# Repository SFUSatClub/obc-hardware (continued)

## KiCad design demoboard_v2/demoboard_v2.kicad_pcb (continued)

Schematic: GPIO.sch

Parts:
D3: LED; L_0402
Q5: DMN2075U; SOT23_DMN2075U
R8, R26: 10k; R_0402
R9: 100; R_0402
U1: TMS570LS0714; LQFP-144_20x20mm_Pitch0.5mm
W13: WD_TEST; Test_Point

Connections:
1v2: U1.17, U1.29, U1.45, U1.48, U1.49, U1.57, U1.87, U1.101, U1.114, U1.123, U1.137, U1.143; also elsewhere on the board
3v3: R9.1, U1.10, U1.26, U1.42, U1.66, U1.69, U1.104, U1.120, U1.134, U1.136; also elsewhere on the board
AD1_3: U1.74; also elsewhere on the board
AD1_4: U1.76; also elsewhere on the board
AD1_5: U1.78; also elsewhere on the board
AD1_6: U1.80; also elsewhere on the board
AD1_7: U1.61; also elsewhere on the board
AD1_8: U1.83; also elsewhere on the board
AD1_9: U1.70; also elsewhere on the board
AD1_10: U1.72; also elsewhere on the board
FLASH0_CS: U1.105; also elsewhere on the board
FLASH1_CS: U1.130; also elsewhere on the board
FLASH2_CS: U1.40; also elsewhere on the board
FLASH_CLK: U1.95; also elsewhere on the board
FLASH_MISO: U1.94; also elsewhere on the board
FLASH_MOSI: U1.93; also elsewhere on the board
GIOA0: U1.2; also elsewhere on the board
GIOA1: U1.5
GIOA2: U1.9
GIOA6: Q5.2 (G), R8.1, U1.16
GIOA7: U1.22
GIOB1: U1.133; also elsewhere on the board
GIOB2: U1.142; also elsewhere on the board
GIOB3: U1.1; also elsewhere on the board
GND: Q5.3 (S), R8.2, R26.2, U1.11, U1.21, U1.27, U1.28, U1.34, U1.43, U1.44, U1.47, U1.50, U1.56, U1.67, U1.68, U1.88, U1.102, U1.103, U1.115, U1.121, U1.122, U1.135, U1.138, U1.144; also elsewhere on the board
I2C_SCL: U1.3; also elsewhere on the board
I2C_SDA: U1.4; also elsewhere on the board
INA_OUT: U1.73; also elsewhere on the board
MASTER_RESET: U1.46; also elsewhere on the board
NHET1_4: U1.36; also elsewhere on the board
NHET1_7: U1.33; also elsewhere on the board
NHET1_22: U1.15; also elsewhere on the board
NHET1_26: U1.92; also elsewhere on the board
unnamed 40: U1.19; also elsewhere on the board
unnamed 41: U1.18; also elsewhere on the board
unnamed 42: U1.20; also elsewhere on the board
unnamed 44: U1.116; also elsewhere on the board
unnamed: D3.1, Q5.1 (D)
unnamed: D3.2, R9.2
unnamed 86: U1.97; also elsewhere on the board
unnamed 93: U1.55; also elsewhere on the board
unnamed 107: U1.86; also elsewhere on the board
unnamed 112: U1.117; also elsewhere on the board
RF_ADC1: U1.60; also elsewhere on the board
RF_ADC2: U1.71; also elsewhere on the board
RF_CLK: U1.53; also elsewhere on the board
RF_CS: U1.37; also elsewhere on the board
RF_GAIN_CS: U1.6; also elsewhere on the board
RF_MISO: U1.51; also elsewhere on the board
RF_MOSI: U1.52; also elsewhere on the board
RF_PWM1: U1.140; also elsewhere on the board
RF_PWM2: U1.141; also elsewhere on the board
RTCK: U1.113; also elsewhere on the board
RTC_CLK: U1.25; also elsewhere on the board
RTC_CS: U1.24; also elsewhere on the board
RTC_MISO: U1.31; also elsewhere on the board
RTC_MOSI: U1.30; also elsewhere on the board
SPI5_CLK: U1.100; also elsewhere on the board
SPI5_CS0: U1.32; also elsewhere on the board
SPI5_MISO: U1.98; also elsewhere on the board
SPI5_MOSI: U1.99; also elsewhere on the board
TCK: U1.112; also elsewhere on the board
TDI: U1.110; also elsewhere on the board
TDO: U1.111; also elsewhere on the board
TMS: U1.108; also elsewhere on the board
UART_RX: U1.38; also elsewhere on the board
UART_TX: U1.39; also elsewhere on the board
WATCHDOG: R26.1, U1.126, W13.1; also elsewhere on the board
nTRST: U1.109; also elsewhere on the board

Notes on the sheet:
"Pin 16 LED" - for blinky debug

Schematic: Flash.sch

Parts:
C24, C25, C26: 0.1µF; C_0402
P9: FLASH_SPI; 3x_01In_Header_v2
P10: FLASH_CS; 3x_01In_Header_v2
R10, R11, R13, R14, R15, R17, R18, R19, R21: 10k; R_0402
R12, R16, R20: 0; R_0402
U5, U6, U7: FLASH_IS25LP016D; SOT-8_208mil_medium
W1, W2, W3, W4, W5, W6: TEST_1P; Test_Point

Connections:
3v3: C24.2, C25.2, C26.2, R11.1, R13.1, R15.1, R17.1, R19.1, R21.1, U5.8, U6.8, U7.8; also elsewhere on the board
FLASH0_CS: P10.3, R11.2, U5.1; also elsewhere on the board
FLASH1_CS: P10.2, R15.2, U6.1; also elsewhere on the board
FLASH2_CS: P10.1, R19.2, U7.1; also elsewhere on the board
FLASH_CLK: P9.1, U5.6, U6.6, U7.6; also elsewhere on the board
FLASH_MISO: P9.2, U5.2, U6.2, U7.2; also elsewhere on the board
FLASH_MOSI: P9.3, U5.5, U6.5, U7.5; also elsewhere on the board
GND: C24.1, C25.1, C26.1, R10.2, R14.2, R18.2, U5.4, U6.4, U7.4; also elsewhere on the board
MASTER_RESET: R12.1, R16.1, R20.1; also elsewhere on the board
unnamed: R10.1, U5.3, W1.1
unnamed: R12.2, R13.2, U5.7, W2.1
unnamed: R14.1, U6.3, W3.1
unnamed: R16.2, R17.2, U6.7, W4.1
unnamed: R18.1, U7.3, W5.1
unnamed: R20.2, R21.2, U7.7, W6.1

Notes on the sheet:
Note: Only connect one of these at once. MASTER_RESET enables simultaneous memory and processor reset, with appropriate bits set.
Triple redundant memory with configurable hold/reset. Hold will pause comms, reset will reset and can be set to be synchronous with processor reset through MASTER_RESET

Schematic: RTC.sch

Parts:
C29: 10nF; C_0402
C30: 470µF; Supercap_v2
P8: RTC_SPI; 4x01In_Header_v2
U8: AB-RTCMC-EOA9-S3; RTC_AB-RTCMC_EA09_S3
W9: CLKOUT; Test_Point
W10: RTC_OE; Test_Point
W11: RTC_INT; Test_Point

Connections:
3v3: C29.1, U8.2 (VDD); also elsewhere on the board
GND: C29.2, C30.2, U8.6 (GND); also elsewhere on the board
unnamed: C30.1, U8.9 (Vbackup)
unnamed: U8.1 (CLKOE), W10.1
unnamed: U8.3 (CLKOUT), W9.1
unnamed: U8.7 (INT), W11.1
RTC_CLK: P8.2, U8.4 (SCL); also elsewhere on the board
RTC_CS: P8.1, U8.8 (CE); also elsewhere on the board
RTC_MISO: P8.3, U8.5 (SDO); also elsewhere on the board
RTC_MOSI: P8.4, U8.10 (SDI); also elsewhere on the board

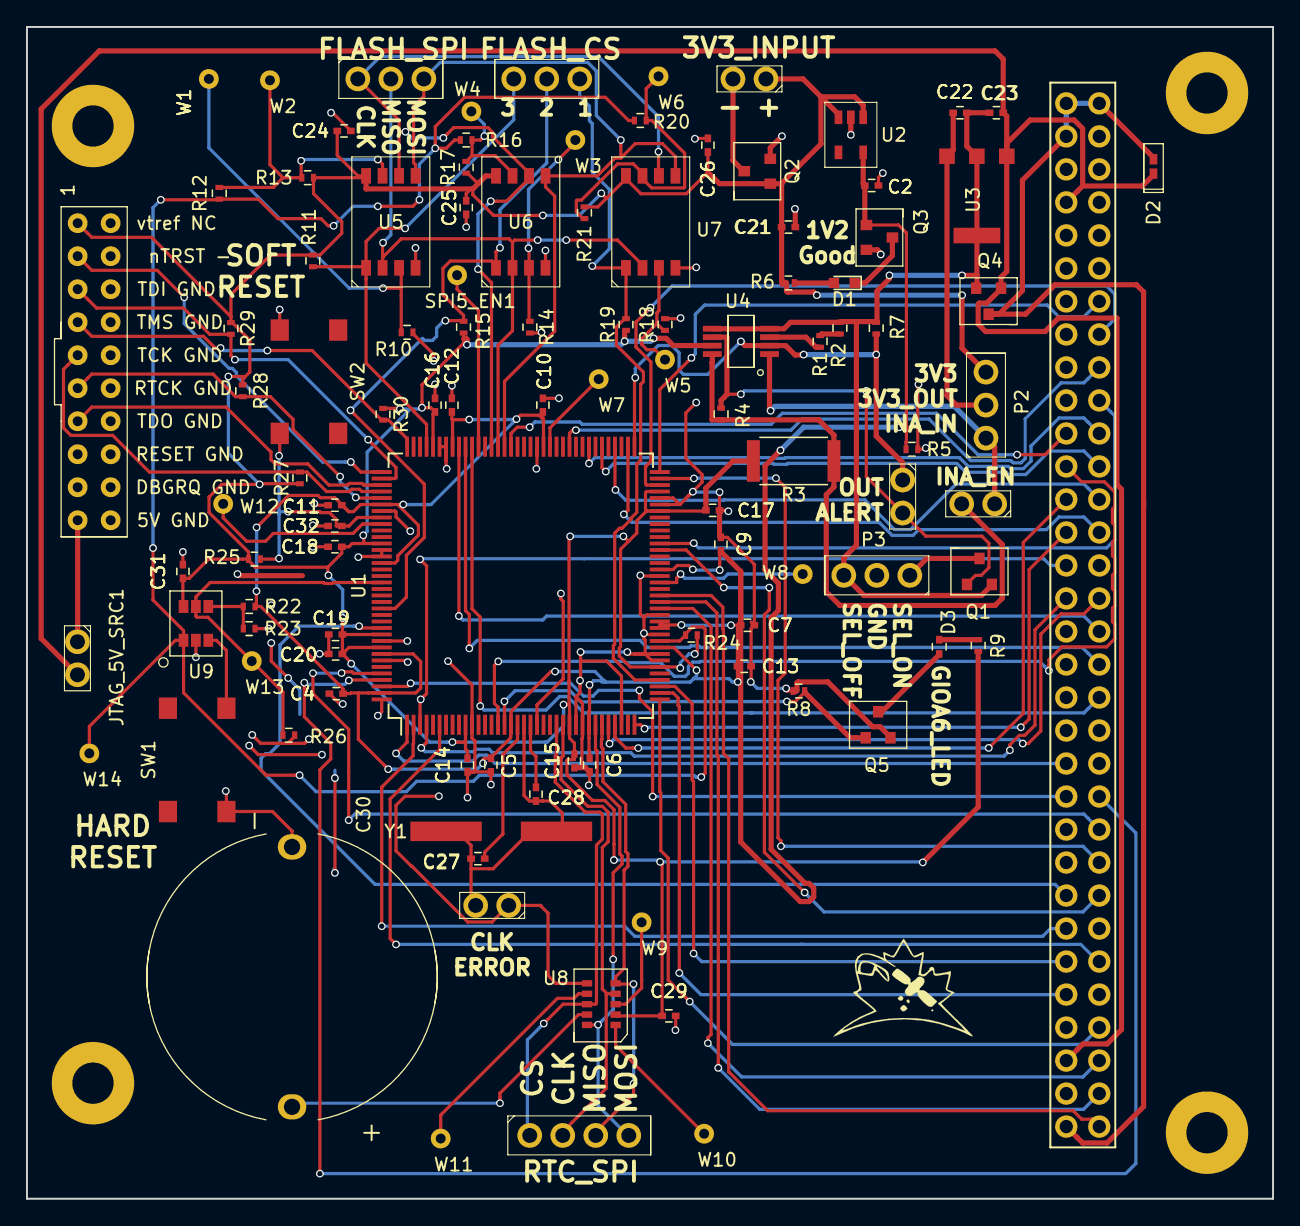
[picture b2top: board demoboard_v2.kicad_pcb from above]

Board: 2 copper layers, 95.9 x 90.2 mm, 107 parts (0 on the bottom side), 92 nets.

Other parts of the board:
SPI5_EN1: TEST_1P; Test_Point
W1#2: TEST_1P; Test_Point

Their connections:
unnamed 86: SPI5_EN1.1; also elsewhere on the board

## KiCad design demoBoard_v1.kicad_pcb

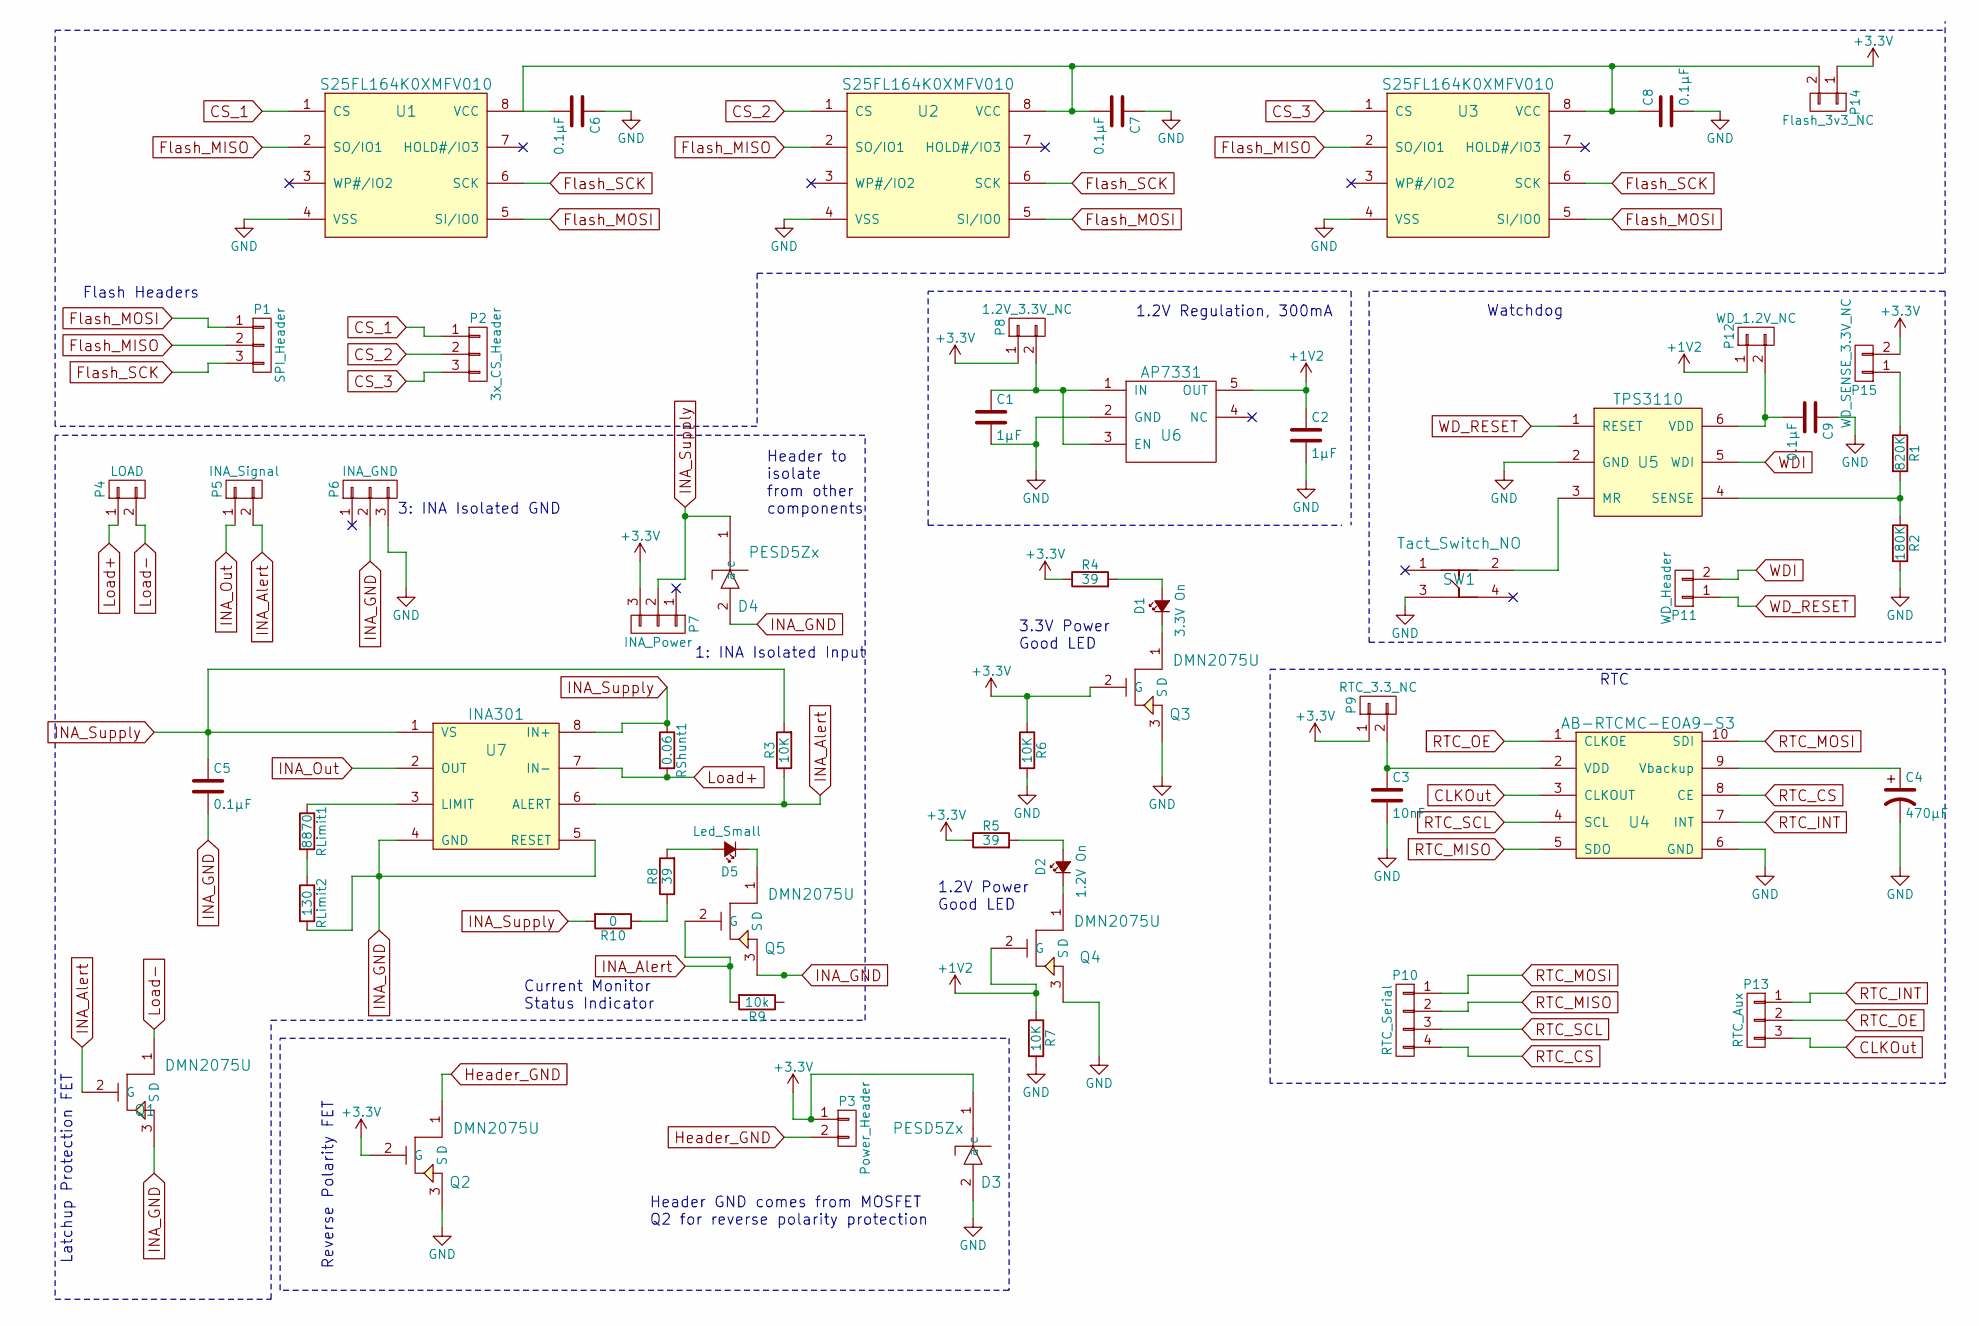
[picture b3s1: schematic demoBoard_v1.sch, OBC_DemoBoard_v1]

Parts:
C1, C2: 1µF; C_0402
C3: 10nF; C_0402
C4: 470µF; Supercap_v2
C5, C6, C7, C8, C9: 0.1µF; C_0402
D1: 3.3V On; LED_150060GS75000
D2: 1.2V On; LED_150060GS75000
D3, D4: PESD5Zx; PESD57zx
D5: Led_Small; LED_150060GS75000
P1: SPI_Header; 3x_01In_Header_v2
P2: 3x_CS_Header; 3x_01In_Header_v2
P3: Power_Header; 2x01In_Header_v2
P4: LOAD; 2x01In_Header_v2
P5: INA_Signal; 2x01In_Header_v2
P6: INA_GND; 3x_01In_Header_v2
P7: INA_Power; 3x_01In_Header_v2
P8: 1.2V_3.3V_NC; 2x01In_Header_v2
P9: RTC_3.3_NC; 2x01In_Header_v2
P10: RTC_Serial; 4x01In_Header_v2
P11: WD_Header; 2x01In_Header_v2
P12: WD_1.2V_NC; 2x01In_Header_v2
P13: RTC_Aux; 3x_01In_Header_v2
P14: Flash_3v3_NC; 2x01In_Header_v2
P15: WD_SENSE_3.3V_NC; 2x01In_Header_v2
Q1, Q2, Q3, Q4, Q5: DMN2075U; SOT23_DMN2075U
R1: 820K; R_0402
R2: 180K; R_0402
R3, R6, R7: 10K; R_0402
R4, R5, R8: 39; R_0402
R9: 10k; R_0402
R10: 0; R_0402
RLimit1: 8870; R_0402
RLimit2: 130; R_0402
RShunt1: 0.06; R_2512
SW1: Tact_Switch_NO; Tact_SW_SMD
U1, U2, U3: S25FL164K0XMFV010; SOT-8_208mil_medium
U4: AB-RTCMC-EOA9-S3; RTC_AB-RTCMC_EA09_S3
U5: TPS3110; SOT_23_6
U6: AP7331; SOT25
U7: INA301; VSSOP_8

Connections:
+1V2: C2.1, P12.1, Q4.2 (G), R7.1, U6.5 (OUT)
+3V3: D3.1 (c), P3.1, P7.3, P8.1, P9.1, P14.1, P15.2, Q2.2 (G), Q3.2 (G), R4.1, R5.1, R6.1
CLKOut: P13.3, U4.3 (CLKOUT)
CS_1: P2.1, U1.1 (CS)
CS_2: P2.2, U2.1 (CS)
CS_3: P2.3, U3.1 (CS)
Flash_MISO: P1.2, U1.2 (SO/IO1), U2.2 (SO/IO1), U3.2 (SO/IO1)
Flash_MOSI: P1.1, U1.5 (SI/IO0), U2.5 (SI/IO0), U3.5 (SI/IO0)
Flash_SCK: P1.3, U1.6 (SCK), U2.6 (SCK), U3.6 (SCK)
GND: C1.2, C2.2, C3.2, C4.2, C6.1, C7.1, C8.2, C9.1, D3.2 (a), P6.3, Q2.3 (S), Q3.3 (S), Q4.3 (S), R2.2, R6.2, R7.2, SW1.3, U1.4 (VSS), U2.4 (VSS), U3.4 (VSS), U4.6 (GND), U5.2 (GND), U6.2 (GND)
Header_GND: P3.2, Q2.1 (D)
INA_Alert: P5.2, Q1.2 (G), Q5.2 (G), R3.1, R9.2, U7.6 (ALERT)
INA_GND: C5.2, D4.2 (a), P6.2, Q1.3 (S), Q5.3 (S), R9.1, RLimit2.2, U7.4 (GND), U7.5 (RESET)
INA_Out: P5.1, U7.2 (OUT)
INA_Supply: C5.1, D4.1 (c), P7.2, R3.2, R10.2, RShunt1.1, U7.1 (VS), U7.8 (IN+)
Load+: P4.1, RShunt1.2, U7.7 (IN-)
Load-: P4.2, Q1.1 (D)
unnamed: C1.1, P8.2, U6.1 (IN), U6.3 (EN)
unnamed: C3.1, P9.2, U4.2 (VDD)
unnamed: C4.1, U4.9 (Vbackup)
unnamed: C6.2, C7.2, C8.1, P14.2, U1.8 (VCC), U2.8 (VCC), U3.8 (VCC)
unnamed: C9.2, P12.2, U5.6 (VDD)
unnamed: D1.1 (K), Q3.1 (D)
unnamed: D1.2 (A), R4.2
unnamed: D2.1 (K), Q4.1 (D)
unnamed: D2.2 (A), R5.2
unnamed: D5.1 (K), Q5.1 (D)
unnamed: D5.2 (A), R8.2
unnamed: P15.1, R1.1
unnamed: R1.2, R2.1, U5.4 (SENSE)
unnamed: R8.1, R10.1
unnamed: RLimit1.1, U7.3 (LIMIT)
unnamed: RLimit1.2, RLimit2.1
unnamed: SW1.2, U5.3 (MR)
RTC_CS: P10.4, U4.8 (CE)
RTC_INT: P13.1, U4.7 (INT)
RTC_MISO: P10.2, U4.5 (SDO)
RTC_MOSI: P10.1, U4.10 (SDI)
RTC_OE: P13.2, U4.1 (CLKOE)
RTC_SCL: P10.3, U4.4 (SCL)
WDI: P11.2, U5.5 (WDI)
WD_RESET: P11.1, U5.1 (RESET)

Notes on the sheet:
Watchdog
Flash Headers
1.2V Regulation, 300mA
RTC
Header to isolate from other components
1: INA Isolated Input
3: INA Isolated GND
Header GND comes from MOSFET Q2 for reverse polarity protection
Latchup Protection FET
Reverse Polarity FET
3.3V Power Good LED
1.2V Power Good LED
Current Monitor Status Indicator

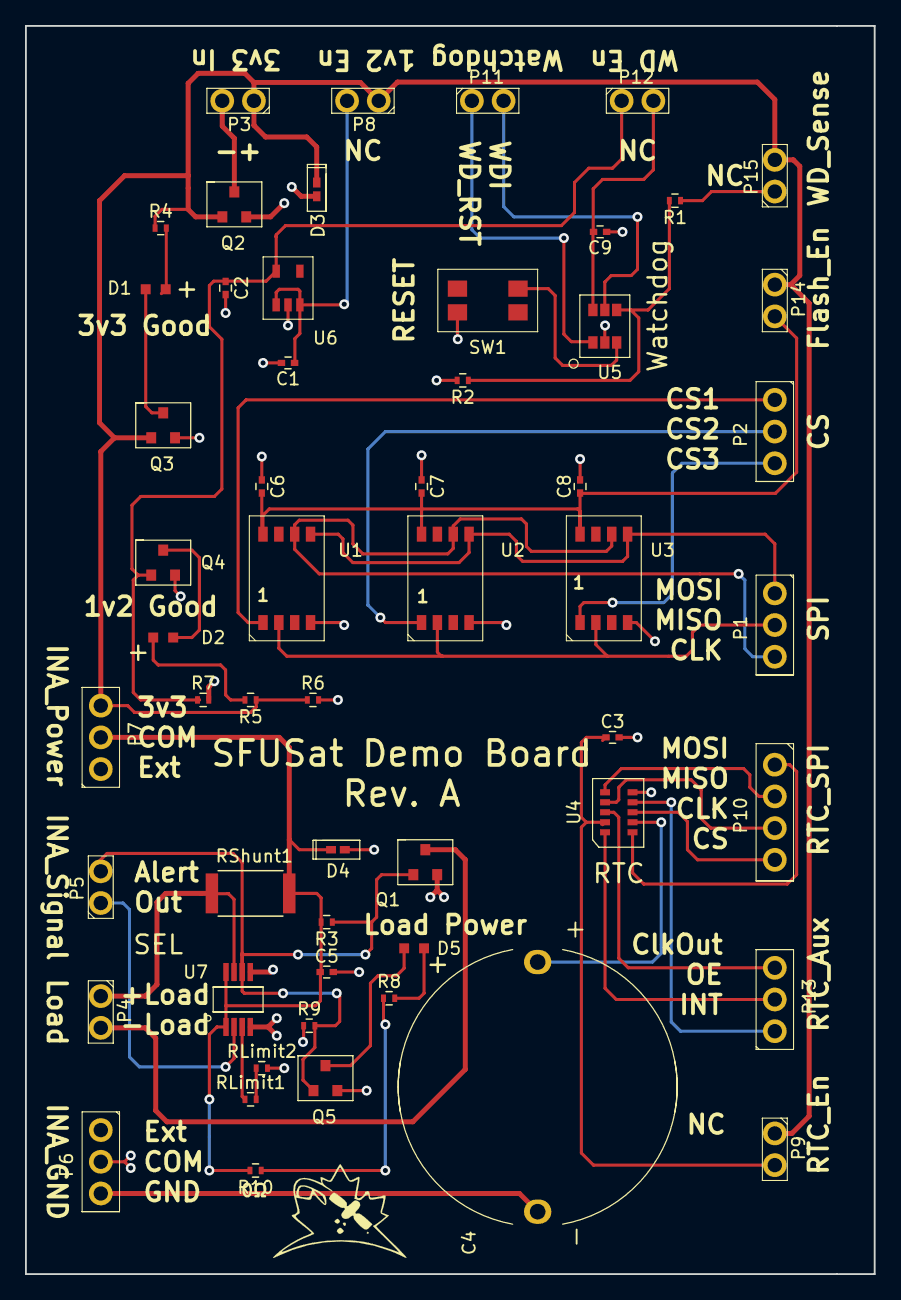
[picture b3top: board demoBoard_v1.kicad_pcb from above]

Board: 2 copper layers, 68.0 x 100.0 mm, 55 parts (0 on the bottom side), 42 nets.

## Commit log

2017-05-10 removed submodule
2017-05-11 added memory interfce and started watchdog
2017-05-19 Nearly done, todo: fix current shunt, add LEDs, add footprints and make PCB
2017-05-22 Todo: change MOSFET and add indicator LEDs
2017-05-22 Updated FET, added indicator LEDs on 3.3v and 1.2v rails.
2017-05-22 Beginning board layout
2017-05-22 Finished initial PCB layout
2017-05-23 Starting to redo things after this commit.
2017-05-23 Cleaned up and made the board smaller. Began adding silkscreen
2017-05-24 Added separate ground pane for SEL monitor to facilitate independent testing of it. Beefed up power tracks. Discovered error with external load connection being shorted to ground at the connector, an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
2017-05-24 Fixed SEL monitor mistake ground connection
2017-05-24 Added more silkscreens including the logo. Reorganized some traces
2017-05-24 Added TVS and INA indicator LED to schematic. Committing before adding footprint and PCB traces.
2017-05-24 Ready to be sent to board house
2017-05-24 Ready to be sent to board house. Last minute changed via size to be safe.
2017-05-24 moved some vias to avoid a silkscreen
2017-05-25 Added gerbers
2017-05-25 add gitignore and update kicad-lib
2017-05-25 fixed gitignore
2017-05-25 Fixed gitignore again lol
2017-05-25 Updated LED resistors to 30 ohm, turned RLimit1 into RLimit1 and RLimit2 which are values you can actually buy. Made pin header holes slightly bigger, regenerated gerbers
2017-05-25 Updated footprints for headers in schematic
2017-05-25 Updated pad clearance to 0.075mm, regenerated gerbers
2017-05-28 Updated footprint lib with solder paste apertures
2017-06-04 Updated submodule KiCad-Lib
2017-06-04 Updated DMN2075 MOSFET symbol
2017-06-04 Updated 0402 capacitor in library. Haven't updated footprints on PCB, although they could be changed.
2017-06-04 Decided to update 0402 resistors and caps to good SFUSat footprints.
2017-06-09 Added LSO743x schematic (not done yet)
2017-06-23 updated Kicad lib with RF changes
2017-06-23 Started new project for board v2, updated footprint for RTC, added all pins of TMS570LS0432
2017-06-30 Added 104 connector, put 104 footprint in PCB and have decoupling caps for the mcu.
2017-06-30 Added RF SPI to schematic
2017-06-30 Added schematics for MCU support
2017-07-04 Beginning to add latchup circuit. Latchup protection can be disabled with jumpers, and now has a current limit of 800mA
2017-07-04 Completed power jumper setup for SEL monitor
2017-07-07 3v3 reverse polarity FET, connected current monitor to ADC, defined RF PWM and ADC pins on 104 connector, added UART connector, pc104 reverse polarity FET, 104 connector TVS diode.
2017-07-12 Added debug LED and 1v2 good LED
2017-07-13 Finished flash memory schematic, added pin 16 LED and 1v2 good LED
2017-07-14 Added clock, RTC, flash serial connections
2017-07-20 Finished watchdog circuit. Todo: add footprint for tact switch, i2c, UART, USB connector
2017-07-21 Beginning board layout.
2017-07-21 Connect RTC CS, CLK, MISO, MOSI
2017-07-21 Checked design rules, placed decoupling for MCU. Beginning placement
2017-07-23 JTAG header added.
2017-07-23 Almost done the layout
2017-07-23 Board layout nearly done - need to add USB jack
2017-07-23 Finished initial layout. USB port added.
2017-07-25 Updating to recent changes
2017-07-25 I think I fixed the mess with the Kicad-Lib submodule
2017-07-25 Removed old nasty Kicad lib from demoboard_v2 directory
2017-07-25 Cleaned up directory structure, added details to readme
2017-07-26 Labels for 104 connector and regulators
2017-07-26 Kicad lib changes?
2017-07-26 Added DS_Store to lib gitignore
2017-07-26 Watchdog enable jumper
2017-07-26 Adjusted solder paste clearance and generated gerbers
2017-07-27 Moved outer trace closer in (top left) and updated gitignore
2017-07-30 Fixing issues raised by board review.
    Orient silkscreen in single direction - done as much as possible.
    Decrease thickness of large font - done.
    Fixed global mask clearance and updated clearence for problematic parts.
    1v2 power net width - 0.25mm can handle 460mA @ 10ºC raise. Max expected is around 360mA (for very brief periods of self test), normal ops are ~150mA.
    Ground island pin 44 of TMS570 - this was always connected, but traces have been re routed to maximize ground plane area.
    Island net U5 - cleaned up the area.
2017-07-30 see previous commit message. Had to add again
2017-07-30 Added 10k pot and removed R2 to allow current limit to be adjusted
2017-07-31 Added FTDI FT230 and beefed up main 1v2 bus lines
2017-07-31 Added gerbers, fixed silkscreen width of USB jumper label
2017-07-31 updated gitignore
2017-07-31 Added gerbers, redid USB section (just need to add differential pair), fixed USB connector paste
2017-07-31 Length mached USB traces and cleaned up FTDI region
2017-07-31 Fixed oscillator circuit.
2017-07-31 Routed signal traces outside of the vicinity of the oscillator
2017-07-31 Cleaned up oscillator traces
2017-07-31 Removed gnd plane from under oscillator, added differential oscillator signal. Generated gerbers
2017-08-01 Cleaned up some floating traces and silkscreens. Generated gerbers for board house
2017-08-01 Fixed a few silkscreens
2017-08-01 Submitted to PCBWay
2017-08-04 Changed 1.2V regulator from AP7331 to XC6222B121MR-G because the 7331 current limit is too low. Also changed C2 from 1µF to 10µF to meet requirements for new regulator
2017-08-17 Updated MCU pin spreadsheet
2017-08-25 Busy wait function created to facilitate quick experimentation. Updated state machine definition to reflect new CONOPS. WIP: fleshing out and integrating the state machine
2018-01-05 Updated spreadsheet, gitignore
2018-01-05 Duplicated v0.3 directory and started renaming process
2018-01-05 generated 0.4 netlist, removed other old stuff. Made board file
2018-01-05 Added board file
2018-01-05 Upstream updates to Kicad-lib
2018-01-07 Temp sensor wiring
    WIP: DIP switch
2018-01-07 Connected A7 to ANTENNA_DEPLOY
    placed DIP switch
    added labels in 104 connector describing GPIO functtionality
2018-01-08 Made GPIO reroutes
    B1: is now RTC alert, also on 104 connector
    A0, A2: labelled as RF_deploy on 104 connector (no routing change)
    A5: RF_IRQ
    A7: ANTENNA_DEPLOY
2018-01-09 Connecte JTAG reset to master reset
2018-01-09 Changed RESET circuitry
    Added jumper to disconnect WD from MASTER_RESET
    Changed SW1 name to "Hard reset via WD"
    Added SW4 - direct connect (not via WD) to MCU. Enables manual hard reset with WD disabled.
2018-01-09 Tied up flash WP, removed flash CS pullup
2018-01-09 Removed option to connect flash WP/RESET to MASTER_RESET
2018-01-09 Spread components, update JTAG footprint
2018-01-09 Board outline, holes
2018-01-09 Placed 104 connector
    also upstream updates from kicad lib
2018-01-09 locked placement of holes, 104, USB
2018-01-09 Bagan placement
2018-01-09 WIP initial placement
2018-01-10 Added labels to all GPIO on 104/chip
    Also added sun sensor ADC to 104 connector
2018-01-17 Added DC in jack for charging
    Also added labels to ADC and GPIO
2018-01-17 Added USB B connector
2018-01-21 Removed trimpot
2018-01-21 Added load connector, switched RTC to MIBSPI5
    RTC on MIBSPI5 because it operates in the same power domain as pretty much everything else. Can now shut off PD3 (though we'd lose I2C access), and the RTC will be fine since it is on PD1.
2018-01-21 Removed GIOA6 pulldown
2018-01-21 Removed JTAG resistors
2018-01-21 Added note about R25, changed value of R24
2018-01-23 Updated to 10 pin JTAG
2018-01-23 Routed xtal
    also removed osc fault jumper
2018-01-23 Initial placement mostly complete
2018-01-23 Routed USB, started reset area
2018-01-24 Latest changes before workshop
2018-01-24 changes from work session - power section mostly done
2018-01-24 Routed all traces to 104 connector. Ugh
2018-01-25 Jan 24th Joe
2018-01-25 Jan 24th Joe evening
2018-01-25 Fixed most DRC issues
2018-01-25 Apparently no unconnected :)
2018-01-25 Mostly finished silk
2018-01-25 Added more silkscreen
    Todo: clean traces, label switches, names, 104 labels
2018-01-26 CLEANUP
2018-01-26 adding final silk
2018-01-30 Sent to PCBWay
2018-02-01 Added dimensions for structural team
2018-02-05 Updated connector symbols to ones in library
2018-02-17 Modified Footprint library path to be relative to KIPRJMOD.
2018-02-17 generated 3d model for rev B_04
2018-02-25 Add silkscreen for RF SPI
2018-03-17 Created v0.5 directory and confirmed that project works
    Let's keep the current PCB and just make changes, instead of redoing the entire layout.
2018-03-17 Updated 1.2v regulator, removed DC jack
2018-03-17 Fixed 104 connector placement
2018-03-18 Removed extraneous 104 connections
2018-03-18 Added required xGPIO, removed 5V from 104 connector
2018-03-18 Removed traces, gen netlist, fixed button footprints
2018-03-18 Cleaned out old stuff
    Fixed library references
2018-03-18 Moved connectors ~3mm outward
    Will reduce the gap between connector edge and the hole in the satellite
2018-03-18 Added 4 more xGPIO
    From CAN peripheral. Currently unused
2018-03-18 Made 4 layer PCB, WIP: decoupling caps
2018-03-19 Updated power setup
    We now either go over USB_5V or through the 104 connector. For flexibility, our own 3V3 header is included, but this is identical to the 104 connector one.
2018-03-19 Routed the nasty stuff
    Needs cleanup but the 104 connector is almost done
2018-03-20 Fixed up 104 section
2018-03-21 WIP PCB
2018-03-21 From video
2018-03-22 layout routing
2018-03-23 FTDI changes
    added test point
2018-03-29 not finished layout routing
2018-03-29 fixed 104 and connections in schematic
2018-03-29 it screwed up the PCB :(
2018-03-29 cleaned up flash
2018-03-29 replaced regulator and temp sensor
2018-03-29 Routed differential pair
2018-03-30 Added logo, finished routing
2018-04-01 Tweaked silkscreen, power section
2018-04-15 relocated USB power enable header
    It will now be accessible from the slot in the side of the satellite
2018-04-15 Added slot-accessible 3v3 input
2018-04-15 various cleanup
2018-04-16 Redo watchdog disable
    We now have two modes: program and space
    - in program mode, watchdog is disabled
    - in space mode, watchdog is enabled
    - uses a MOSFET with gate pulled up normally (to connect watchdog reset and master reset), gate shorted to ground to disconnect master and watchdog resets.
2018-04-16 FTDI is 3V3 powered now
    Before, FTDI was exclusively 5v powered. Since the main supply is now 3.3, we can't do that. Moved to 3.3V
2018-04-16 Added logos
2018-04-20 Added logo, I2c pullup
    - i2c now has pullup resistor pads.
    - added big logo on the bottom side
2018-04-21 Create gerbers, silk tweaks
2018-04-23 Moved pins to fit in access hole
    - moved prog jumper and 3v3 in
    - removed blind/buried vias
